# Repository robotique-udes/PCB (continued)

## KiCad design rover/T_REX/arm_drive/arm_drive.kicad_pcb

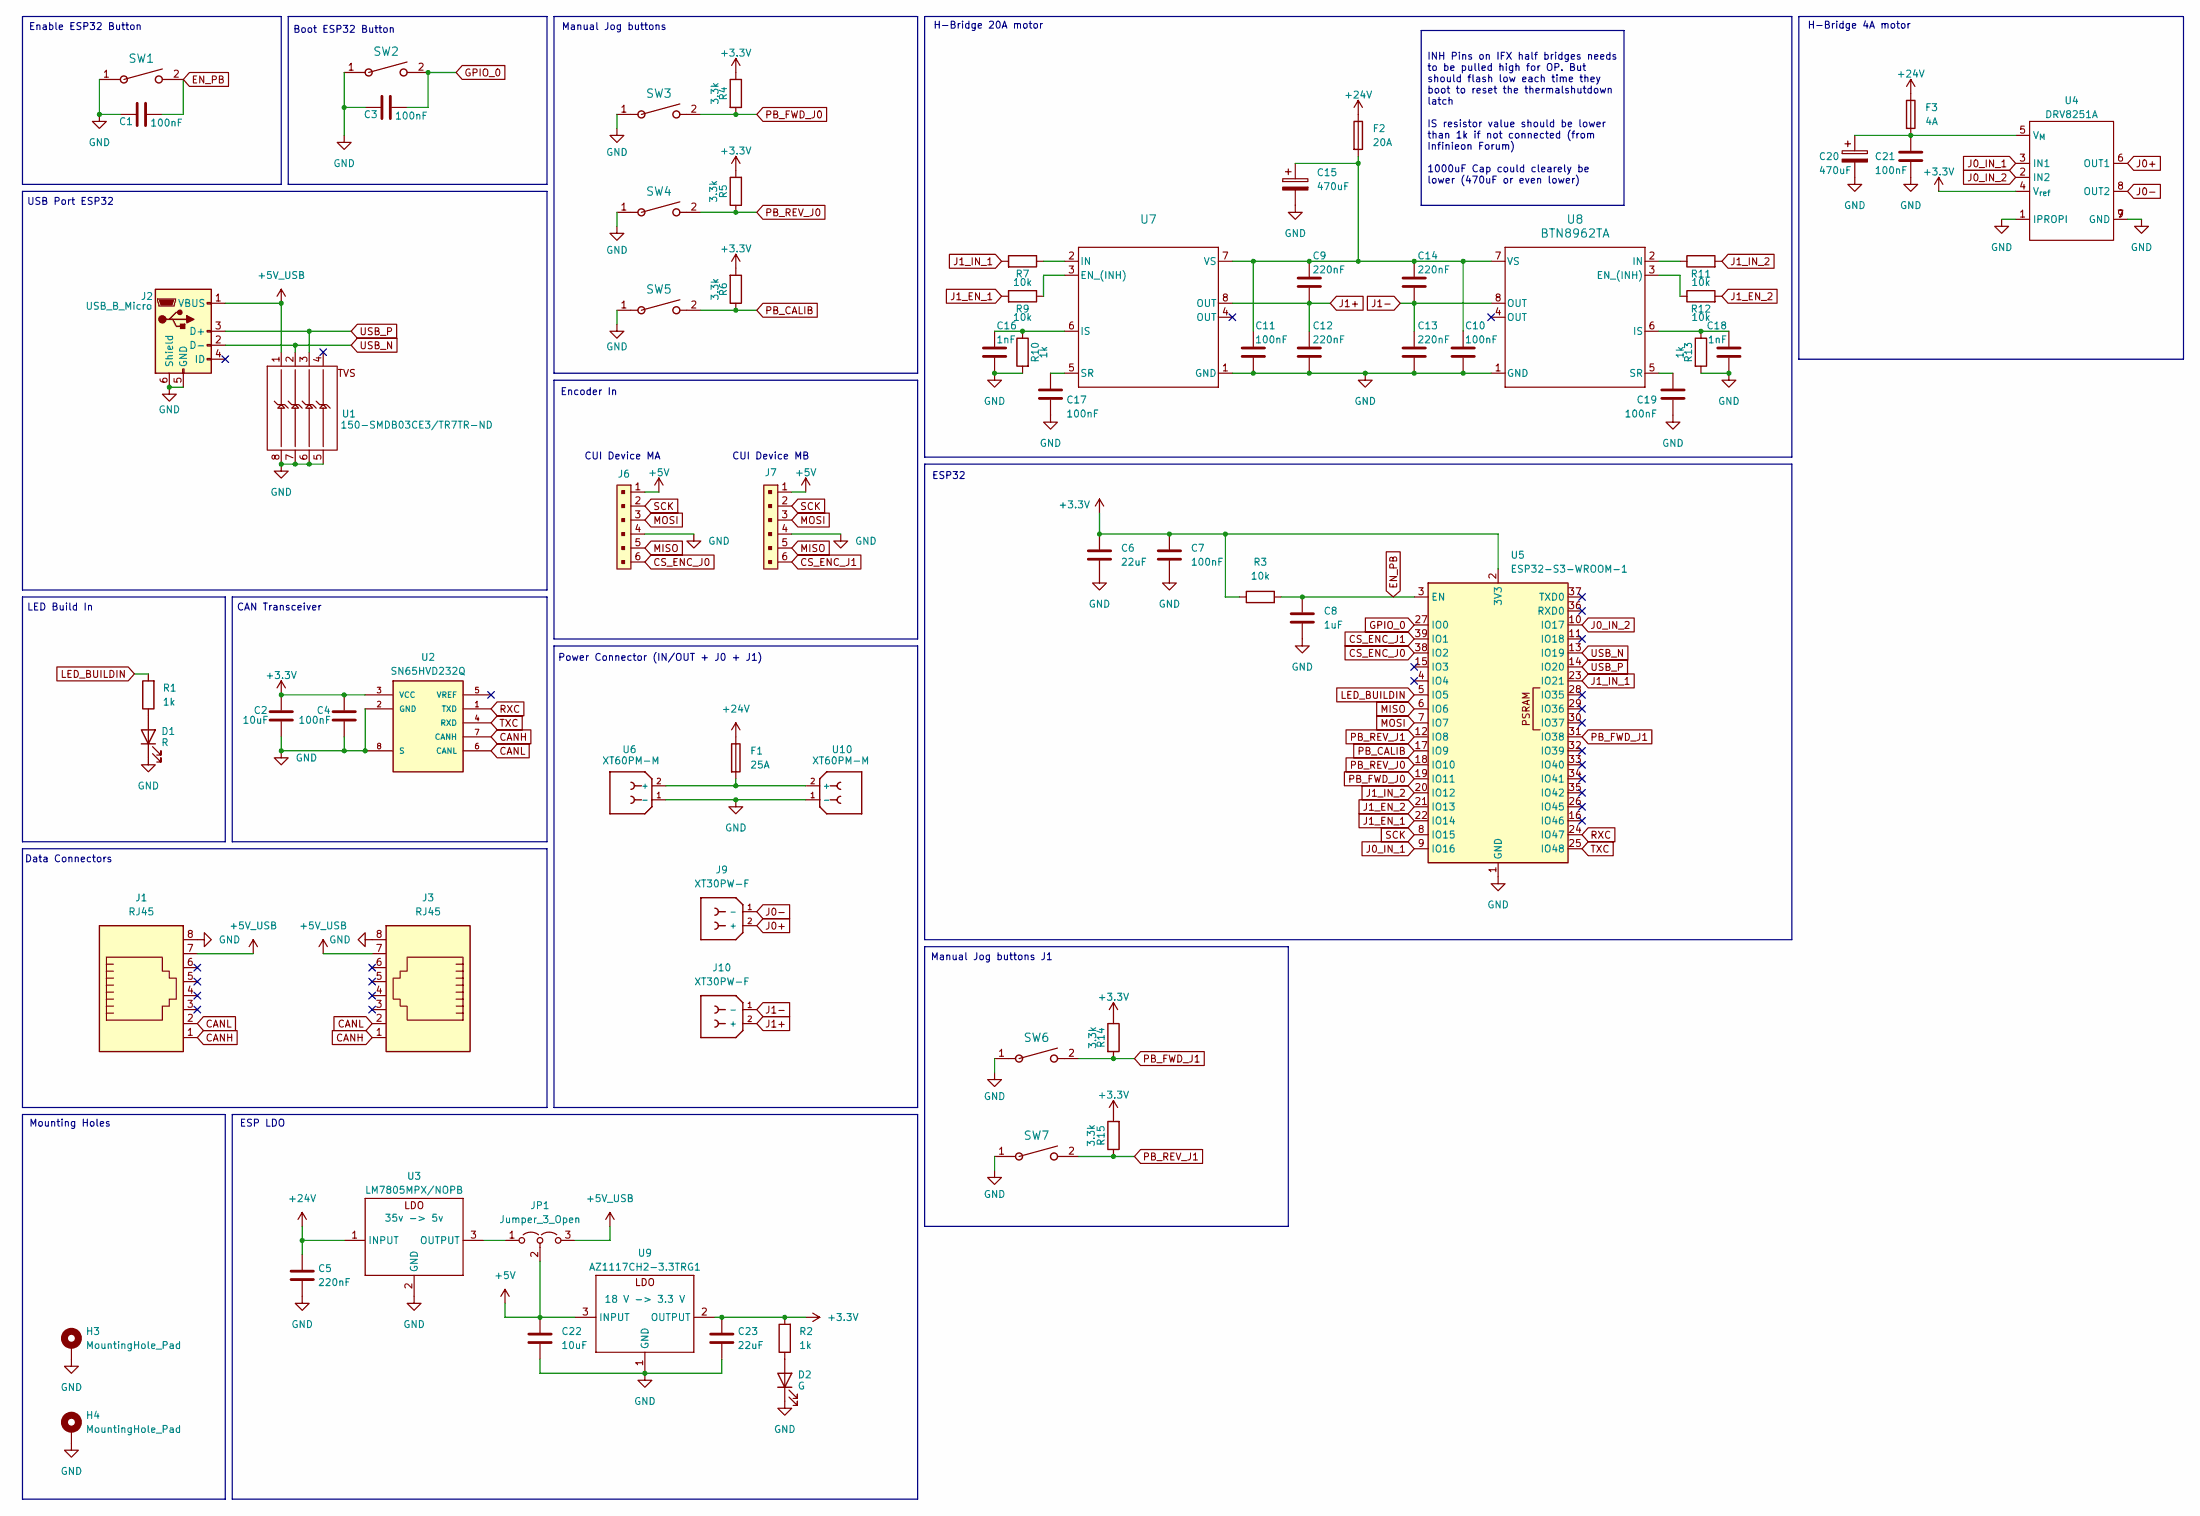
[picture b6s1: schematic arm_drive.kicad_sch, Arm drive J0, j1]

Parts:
C1, C3, C4, C7, C10, C11, C17, C19, C21: 100nF; C_0805_2012Metric_Pad1.18x1.45mm_HandSolder
C2, C22: 10uF; C_0805_2012Metric_Pad1.18x1.45mm_HandSolder
C5, C9, C12, C13, C14: 220nF; C_0805_2012Metric_Pad1.18x1.45mm_HandSolder
C6, C23: 22uF; C_0805_2012Metric_Pad1.18x1.45mm_HandSolder
C8: 1uF; C_0805_2012Metric_Pad1.18x1.45mm_HandSolder
C15, C20: 470uF; CP_Radial_D8.0mm_P3.50mm
C16, C18: 1nF; C_0805_2012Metric_Pad1.18x1.45mm_HandSolder
D1: R; LED_0805_2012Metric_Pad1.15x1.40mm_HandSolder
D2: G; LED_0805_2012Metric_Pad1.15x1.40mm_HandSolder
F1: 25A; FUSE_3568-20
F2: 20A; FUSE_3568-20
F3: 4A; FUSE_3568-20
H3, H4: MountingHole_Pad; MountingHole_3.2mm_M3_DIN965_Pad_TopBottom
J1: RJ45; ASSMANN_A-2014-2-4-N-T-R
J2: USB_B_Micro; USB_Micro-B_Amphenol_10118193-0001LF_Horizontal
J3: RJ45; AMPHENOL_54601-908WPLF
J6, J7: JST_XH_B6B-XH-AM_1x06_P2.50mm_Vertical
J9, J10: XT30PW-F; AMASS_XT30PW-F_1x02_P2.50mm_Horizontal; PARTREV 1.2
JP1: Jumper_3_Open; PinHeader_1x03_P2.54mm_Vertical
R1, R2, R10, R13: 1k; R_0805_2012Metric_Pad1.20x1.40mm_HandSolder
R3, R7, R9, R11, R12: 10k; R_0805_2012Metric_Pad1.20x1.40mm_HandSolder
R4, R5, R6, R14, R15: 3.3k; R_0805_2012Metric_Pad1.20x1.40mm_HandSolder
SW1, SW2, SW3, SW4, SW5, SW6, SW7: TS09-63-25-WT-160-SMT-TR; SW_TS09-63-25_CUD
U1: 150-SMDB03CE3/TR7TR-ND; SOIC-8-1EP_3.9x4.9mm_P1.27mm_EP2.29x3mm
U2: SN65HVD232Q; SOIC127P600X175-8N; PARTREV 4
U3: LM7805MPX/NOPB; SOT-223-3_TabPin2
U4: DRV8251A; Texas_HSOP-8-1EP_3.9x4.9mm_P1.27mm_ThermalVias
U5: ESP32-S3-WROOM-1
U6, U10: XT60PM-M; AMASS_XT60-M_1x02_P7.20mm_Vertical
U7, U8: BTN8962TA; PG-TO263-7-1_INF-M
U9: AZ1117CH2-3.3TRG1; SOT-223-3_TabPin2

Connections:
+3.3V: C2.1, C4.1, C6.1, C7.1, C23.1, R2.2, R3.1, R4.1, R5.2, R6.2, R14.1, R15.2, U2.3 (VCC), U4.4 (V_{ref}), U5.2 (3V3), U9.2 (OUTPUT)
+5V: C22.1, J6.1, J7.1, JP1.2 (C), U9.3 (INPUT)
+5V_USB: J1.7, J2.1 (VBUS), J3.7, JP1.3 (B), U1.1
+24V: C5.1, F1.1, F2.1, F3.1, U3.1 (INPUT)
CANH: J1.1, J3.1, U2.7 (CANH)
CANL: J1.2, J3.2, U2.6 (CANL)
CS_ENC_J0: J6.6, U5.38 (IO2)
CS_ENC_J1: J7.6, U5.39 (IO1)
EN_PB: C1.2, C8.1, R3.2, SW1.2, U5.3 (EN)
GND: C1.1, C2.2, C3.1, C4.2, C5.2, C6.2, C7.2, C8.2, C10.2, C11.2, C12.2, C13.2, C15.2, C16.2, C17.2, C18.2, C19.2, C20.2, C21.2, C22.2, C23.2, D1.1 (K), D2.1 (K), H3.1, H4.1, J1.8, J2.5 (GND), J2.6 (Shield), J3.8, J6.4, J7.4, R10.2, R13.2, SW1.1, SW2.1, SW3.1, SW4.1, SW5.1, SW6.1, SW7.1, U1.5, U1.6, U1.7, U1.8, U2.2 (GND), U2.8 (S), U3.2 (GND), U4.1 (IPROPI), U4.7 (GND), U4.9 (GND), U5.1 (GND), U5.40 (GND), U5.41 (GND), U6.1 (-), U7.1 (GND), U8.1 (GND), U9.1 (GND), U10.1 (-)
GPIO_0: C3.2, SW2.2, U5.27 (IO0)
J0+: J9.2 (+), U4.6 (OUT1)
J0-: J9.1 (-), U4.8 (OUT2)
J0_IN_1: U4.3 (IN1), U5.9 (IO16)
J0_IN_2: U4.2 (IN2), U5.10 (IO17)
J1+: C9.2, C12.1, J10.2 (+), U7.8 (OUT)
J1-: C13.1, C14.2, J10.1 (-), U8.8 (OUT)
J1_EN_1: R9.2, U5.22 (IO14)
J1_EN_2: R12.2, U5.21 (IO13)
J1_IN_1: R7.2, U5.23 (IO21)
J1_IN_2: R11.2, U5.20 (IO12)
LED_BUILDIN: R1.2, U5.5 (IO5)
MISO: J6.5, J7.5, U5.6 (IO6)
MOSI: J6.3, J7.3, U5.7 (IO7)
unnamed: D1.2 (A), R1.1
unnamed: D2.2 (A), R2.1
unnamed: JP1.1 (A), U3.3 (OUTPUT)
unnamed: C20.1, C21.1, F3.2, U4.5 (V_{M})
unnamed: R9.1, U7.3 (EN_(INH))
unnamed: R7.1, U7.2 (IN)
unnamed: C16.1, R10.1, U7.6 (IS)
unnamed: C17.1, U7.5 (SR)
unnamed: C9.1, C10.1, C11.1, C14.1, C15.1, F2.2, U7.7 (VS), U8.7 (VS)
unnamed: R12.1, U8.3 (EN_(INH))
unnamed: R11.1, U8.2 (IN)
unnamed: C18.1, R13.1, U8.6 (IS)
unnamed: C19.1, U8.5 (SR)
unnamed: F1.2, U6.2 (+), U10.2 (+)
PB_CALIB: R6.1, SW5.2, U5.17 (IO9)
PB_FWD_J0: R4.2, SW3.2, U5.19 (IO11)
PB_FWD_J1: R14.2, SW6.2, U5.31 (IO38)
PB_REV_J0: R5.1, SW4.2, U5.18 (IO10)
PB_REV_J1: R15.1, SW7.2, U5.12 (IO8)
RXC: U2.1 (TXD), U5.24 (IO47)
SCK: J6.2, J7.2, U5.8 (IO15)
TXC: U2.4 (RXD), U5.25 (IO48)
USB_N: J2.2 (D-), U1.2, U5.13 (IO19)
USB_P: J2.3 (D+), U1.3, U5.14 (IO20)

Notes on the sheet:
INH Pins on IFX half bridges needs to be pulled high for OP. But should flash low each time they boot to reset the thermalshutdown latch IS resistor value should be lower than 1k if not connected (from Infinieon Forum) 1000uF Cap could clearely be lower (470uF or even lower)
Boot ESP32 Button
LED Build In
Enable ESP32 Button
CAN Transceiver
Encoder In
Power Connector (IN/OUT + J0 + J1)
ESP LDO
CUI Device MB
Manual Jog buttons
Data Connectors
H-Bridge 20A motor
Mounting Holes
USB Port ESP32
CUI Device MA
Manual Jog buttons J1
H-Bridge 4A motor
ESP32

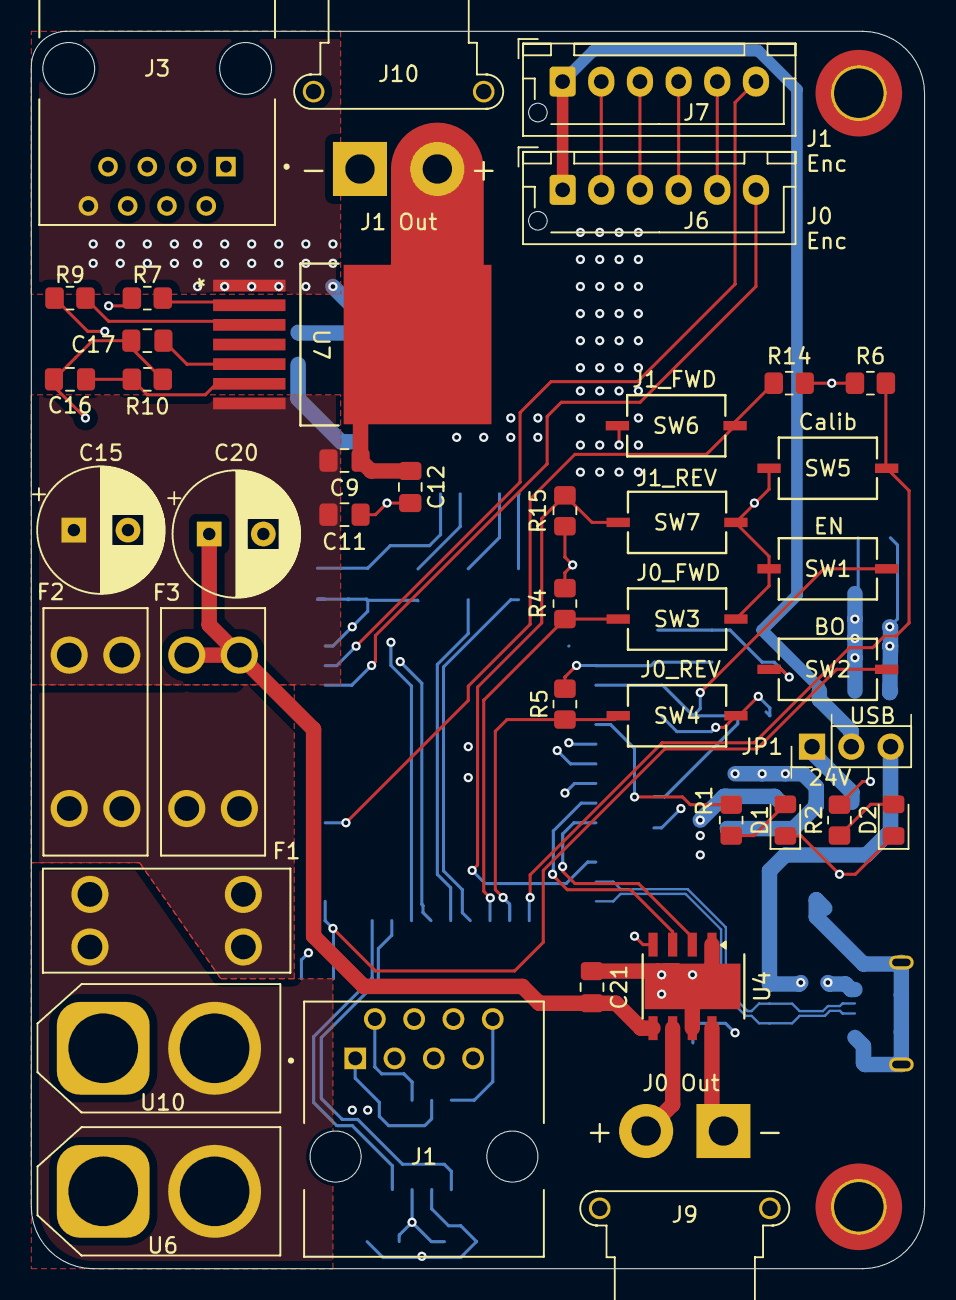
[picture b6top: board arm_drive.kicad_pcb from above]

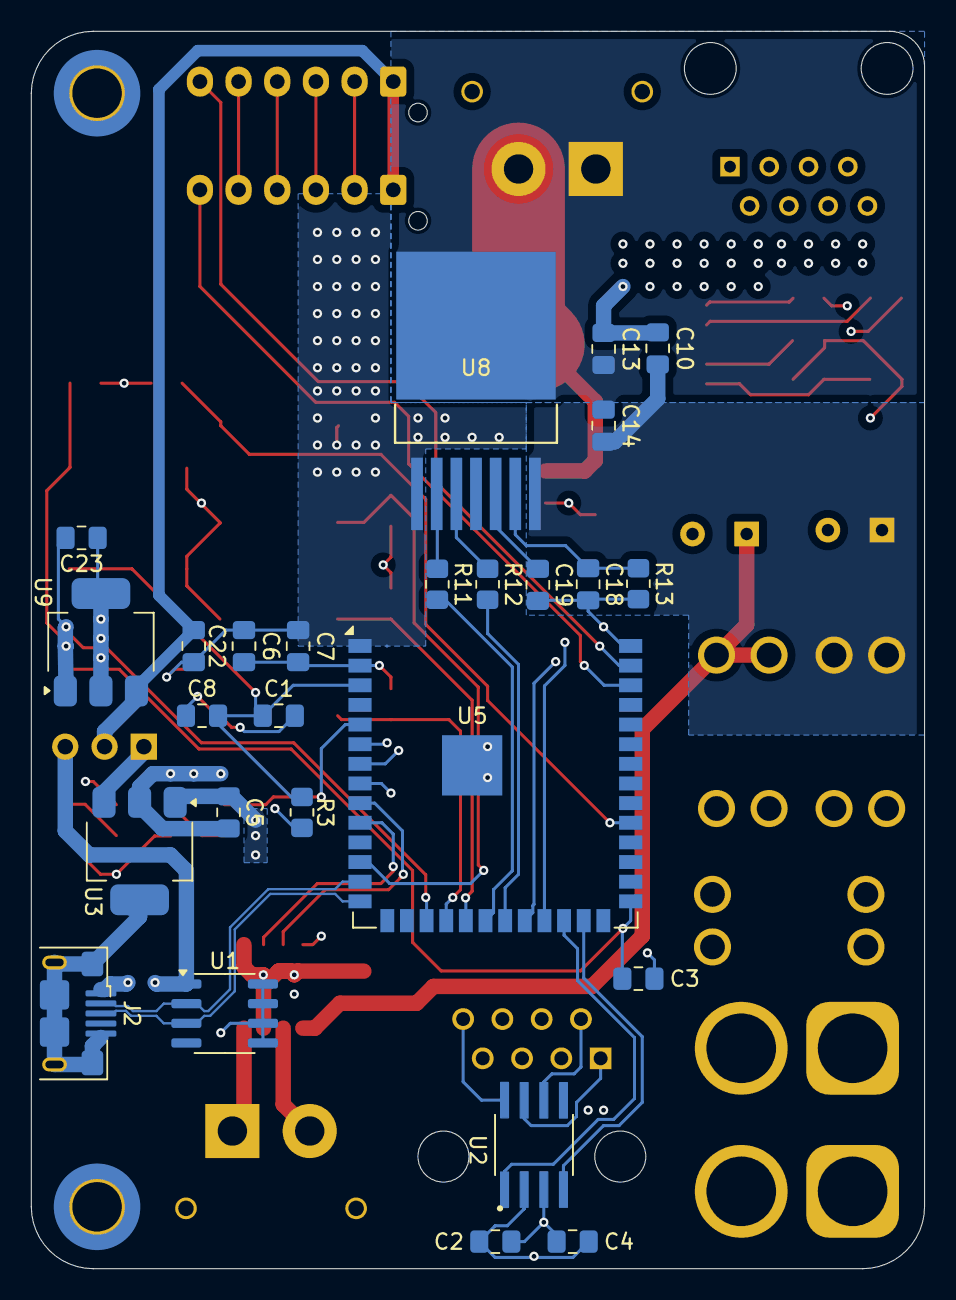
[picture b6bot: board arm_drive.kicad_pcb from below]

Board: 4 copper layers, 57.8 x 80.0 mm, 69 parts (26 on the bottom side), 48 nets.

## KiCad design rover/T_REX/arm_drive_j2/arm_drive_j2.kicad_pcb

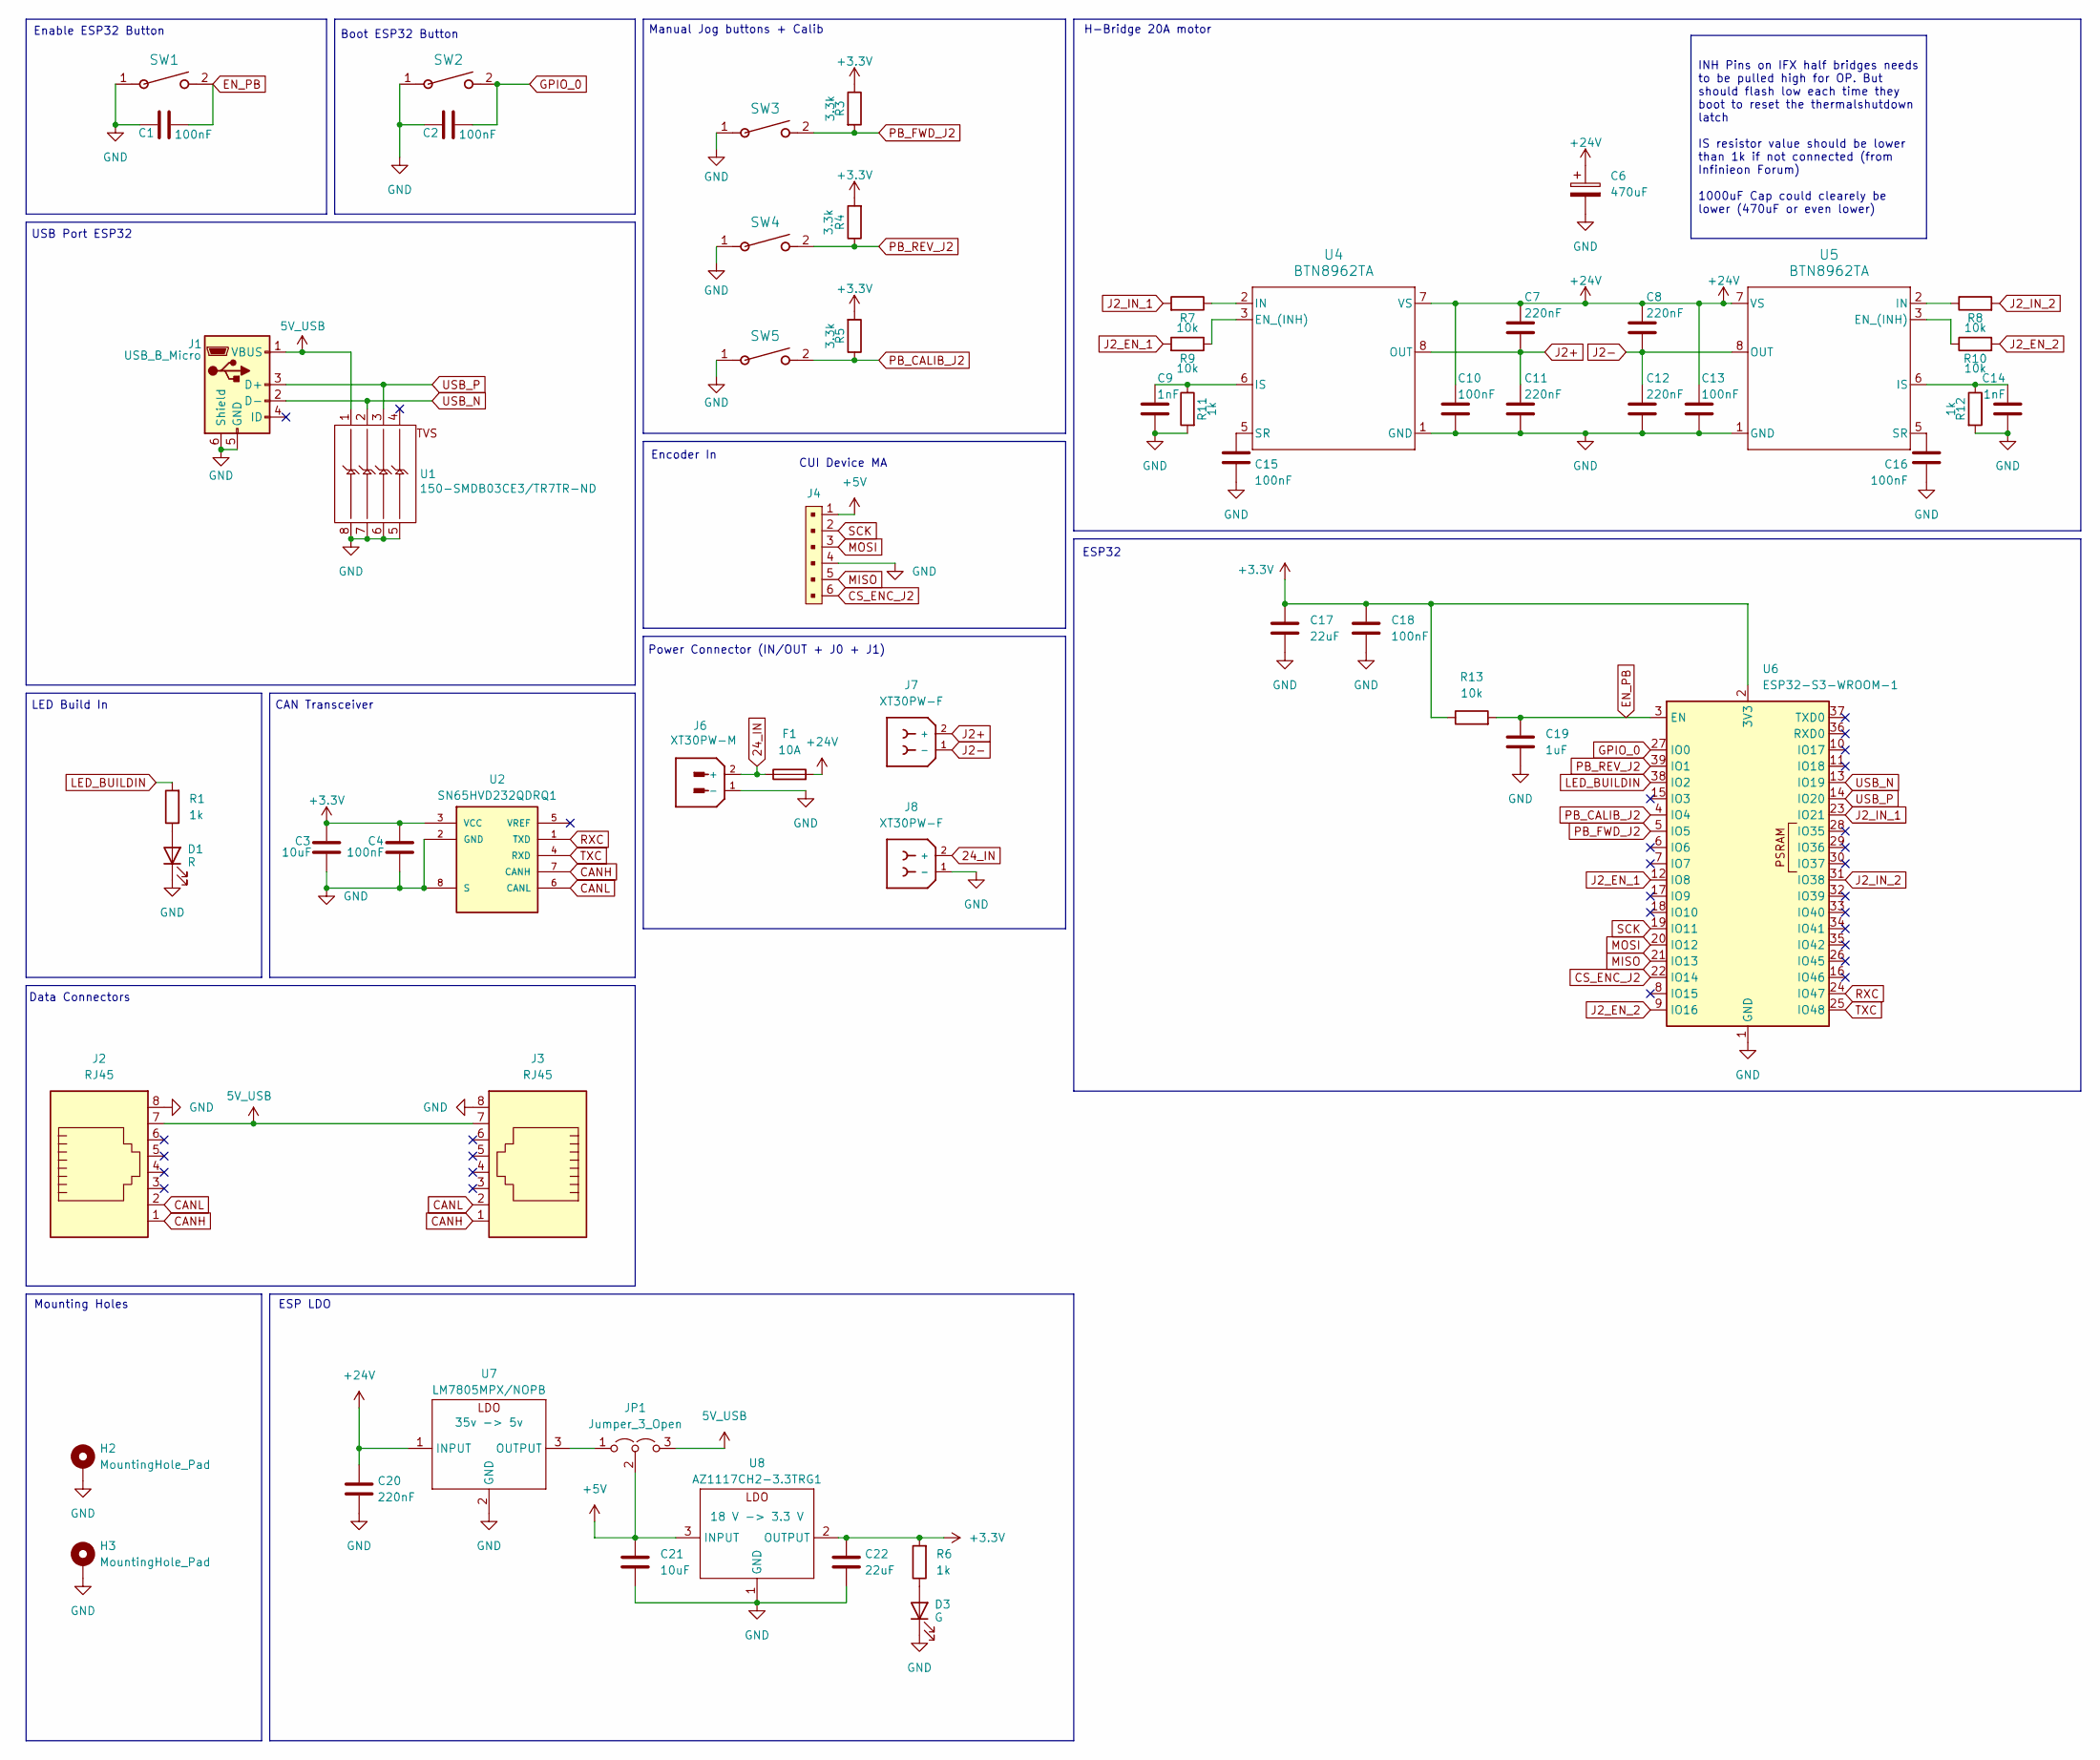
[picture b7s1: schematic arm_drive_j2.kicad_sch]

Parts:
C1, C2, C4, C10, C13, C15, C16, C18: 100nF; C_0805_2012Metric_Pad1.18x1.45mm_HandSolder
C3, C21: 10uF; C_0805_2012Metric_Pad1.18x1.45mm_HandSolder
C6: 470uF; CP_Radial_D12.5mm_P5.00mm
C7, C8, C11, C12, C20: 220nF; C_0805_2012Metric_Pad1.18x1.45mm_HandSolder
C9, C14: 1nF; C_0805_2012Metric_Pad1.18x1.45mm_HandSolder
C17, C22: 22uF; C_0805_2012Metric_Pad1.18x1.45mm_HandSolder
C19: 1uF; C_0805_2012Metric_Pad1.18x1.45mm_HandSolder
D1: R; LED_0805_2012Metric_Pad1.15x1.40mm_HandSolder
D3: G; LED_0805_2012Metric_Pad1.15x1.40mm_HandSolder
F1: 10A; FUSE_3568-20
H2, H3: MountingHole_Pad; MountingHole_2.2mm_M2_DIN965_Pad_TopBottom
J1: USB_B_Micro; USB_Micro-B_Amphenol_10118193-0001LF_Horizontal
J2, J3: RJ45; AMPHENOL_54601-908WPLF
J4: CONN_S6B-XH-SM4-TB_JST
J6: XT30PW-M; AMASS_XT30PW-M_1x02_P2.50mm_Horizontal; PARTREV 1.2
J7, J8: XT30PW-F; AMASS_XT30PW-F_1x02_P2.50mm_Horizontal; PARTREV 1.2
JP1: Jumper_3_Open; PinHeader_1x03_P2.54mm_Vertical
R1, R6, R11, R12: 1k; R_0805_2012Metric_Pad1.20x1.40mm_HandSolder
R3, R4, R5: 3.3k; R_0805_2012Metric_Pad1.20x1.40mm_HandSolder
R7, R8, R9, R10, R13: 10k; R_0805_2012Metric_Pad1.20x1.40mm_HandSolder
SW1, SW2, SW3, SW4, SW5: TS09-63-25-WT-160-SMT-TR; SW_TS09-63-25_CUD
U1: 150-SMDB03CE3/TR7TR-ND; SOIC-8-1EP_3.9x4.9mm_P1.27mm_EP2.29x3mm
U2: SN65HVD232QDRQ1; SOIC127P600X175-8N; PARTREV 4
U4, U5: BTN8962TA; PG-TO263-7-1_INF-M
U6: ESP32-S3-WROOM-1
U7: LM7805MPX/NOPB; SOT-223-3_TabPin2
U8: AZ1117CH2-3.3TRG1; SOT-223-3_TabPin2

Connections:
5V_USB: J1.1 (VBUS), J2.7, J3.7, JP1.3 (B), U1.1
24_IN: F1.1, J6.2 (+), J8.2 (+)
+3.3V: C3.1, C4.1, C17.1, C18.1, C22.1, R3.1, R4.2, R5.2, R6.2, R13.1, U2.3 (VCC), U6.2 (3V3), U8.2 (OUTPUT)
+5V: C21.1, J4.1, JP1.2 (C), U8.3 (INPUT)
+24V: C6.1, C7.1, C8.1, C10.1, C13.1, C20.1, F1.2, U4.7 (VS), U5.7 (VS), U7.1 (INPUT)
CANH: J2.1, J3.1, U2.7 (CANH)
CANL: J2.2, J3.2, U2.6 (CANL)
CS_ENC_J2: J4.6, U6.22 (IO14)
EN_PB: C1.2, C19.1, R13.2, SW1.2, U6.3 (EN)
GND: C1.1, C2.1, C3.2, C4.2, C6.2, C9.2, C10.2, C11.2, C12.2, C13.2, C14.2, C15.2, C16.2, C17.2, C18.2, C19.2, C20.2, C21.2, C22.2, D1.1 (K), D3.1 (K), H2.1, H3.1, J1.5 (GND), J1.6 (Shield), J2.8, J3.8, J4.4, J6.1 (-), J8.1 (-), R11.2, R12.2, SW1.1, SW2.1, SW3.1, SW4.1, SW5.1, U1.5, U1.6, U1.7, U1.8, U2.2 (GND), U2.8 (S), U4.1 (GND), U5.1 (GND), U6.1 (GND), U6.40 (GND), U6.41 (GND), U7.2 (GND), U8.1 (GND)
GPIO_0: C2.2, SW2.2, U6.27 (IO0)
J2+: C7.2, C11.1, J7.2 (+), U4.8 (OUT)
J2-: C8.2, C12.1, J7.1 (-), U5.8 (OUT)
J2_EN_1: R9.2, U6.12 (IO8)
J2_EN_2: R10.2, U6.9 (IO16)
J2_IN_1: R7.2, U6.23 (IO21)
J2_IN_2: R8.2, U6.31 (IO38)
LED_BUILDIN: R1.2, U6.38 (IO2)
MISO: J4.5, U6.21 (IO13)
MOSI: J4.3, U6.20 (IO12)
unnamed: D1.2 (A), R1.1
unnamed: D3.2 (A), R6.1
unnamed: JP1.1 (A), U7.3 (OUTPUT)
unnamed: R9.1, U4.3 (EN_(INH))
unnamed: R7.1, U4.2 (IN)
unnamed: C9.1, R11.1, U4.6 (IS)
unnamed: C15.1, U4.5 (SR)
unnamed: R10.1, U5.3 (EN_(INH))
unnamed: R8.1, U5.2 (IN)
unnamed: C14.1, R12.1, U5.6 (IS)
unnamed: C16.1, U5.5 (SR)
PB_CALIB_J2: R5.1, SW5.2, U6.4 (IO4)
PB_FWD_J2: R3.2, SW3.2, U6.5 (IO5)
PB_REV_J2: R4.1, SW4.2, U6.39 (IO1)
RXC: U2.1 (TXD), U6.24 (IO47)
SCK: J4.2, U6.19 (IO11)
TXC: U2.4 (RXD), U6.25 (IO48)
USB_N: J1.2 (D-), U1.2, U6.13 (IO19)
USB_P: J1.3 (D+), U1.3, U6.14 (IO20)

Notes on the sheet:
INH Pins on IFX half bridges needs to be pulled high for OP. But should flash low each time they boot to reset the thermalshutdown latch IS resistor value should be lower than 1k if not connected (from Infinieon Forum) 1000uF Cap could clearely be lower (470uF or even lower)
Boot ESP32 Button
LED Build In
Enable ESP32 Button
CAN Transceiver
Encoder In
Power Connector (IN/OUT + J0 + J1)
ESP LDO
Manual Jog buttons + Calib
Data Connectors
H-Bridge 20A motor
Mounting Holes
USB Port ESP32
CUI Device MA
ESP32

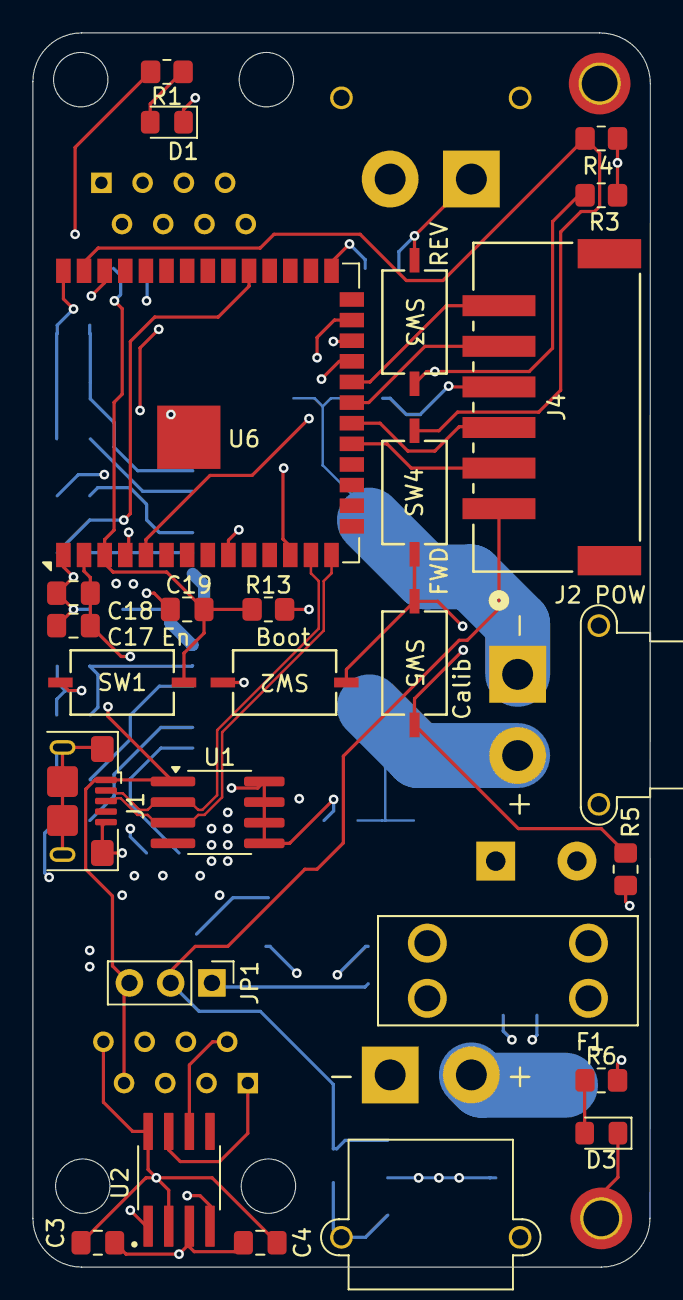
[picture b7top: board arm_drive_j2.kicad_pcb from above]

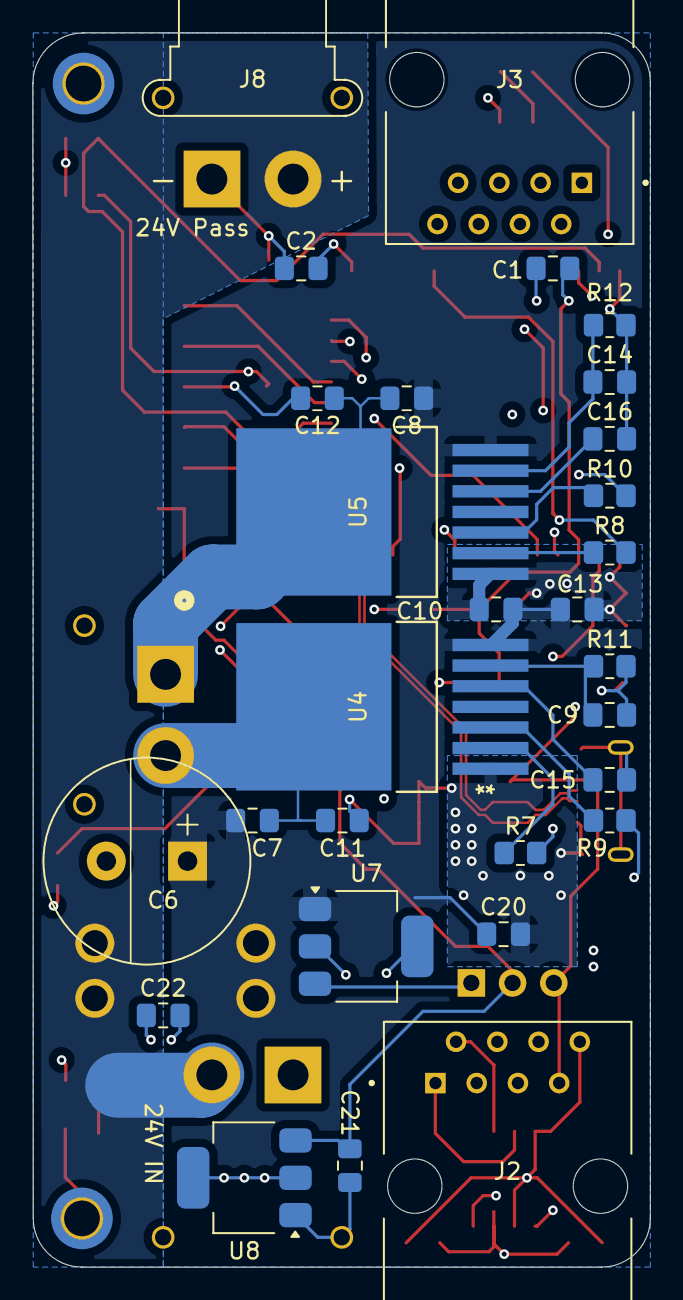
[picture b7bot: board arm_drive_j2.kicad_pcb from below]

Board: 4 copper layers, 38.0 x 76.0 mm, 58 parts (29 on the bottom side), 39 nets.

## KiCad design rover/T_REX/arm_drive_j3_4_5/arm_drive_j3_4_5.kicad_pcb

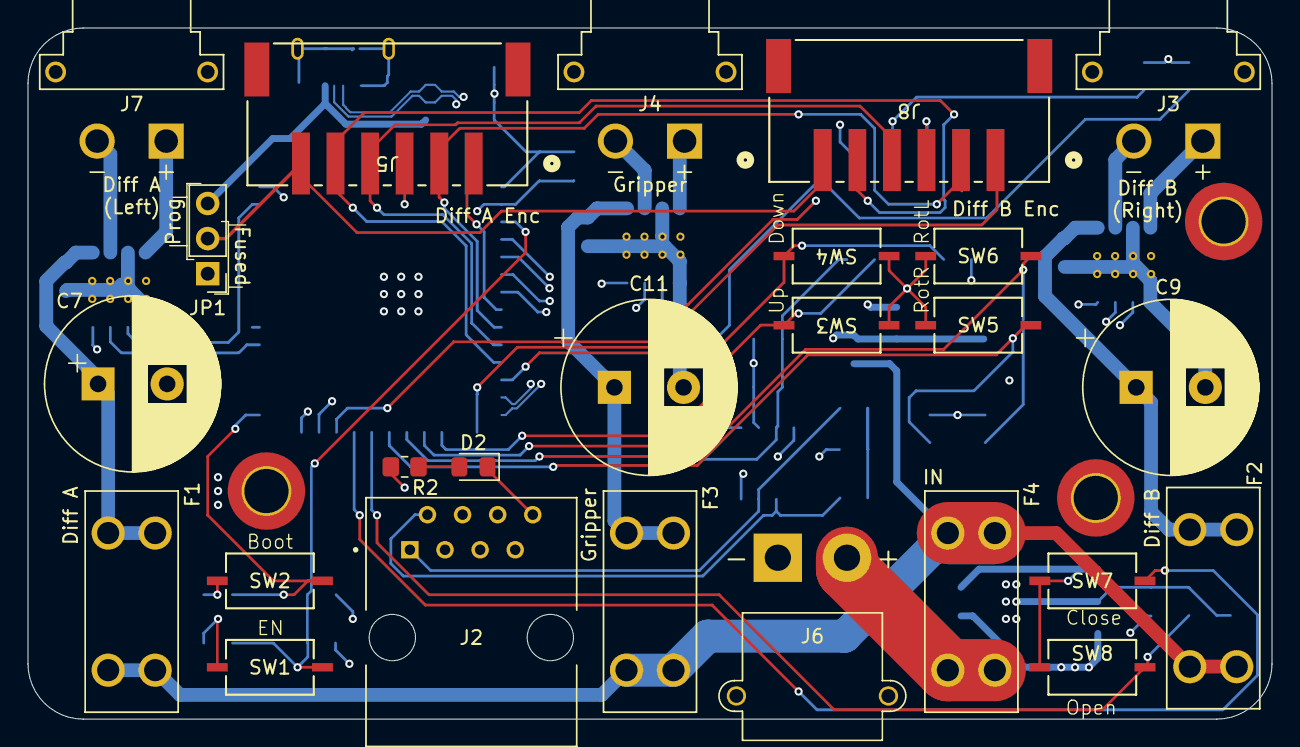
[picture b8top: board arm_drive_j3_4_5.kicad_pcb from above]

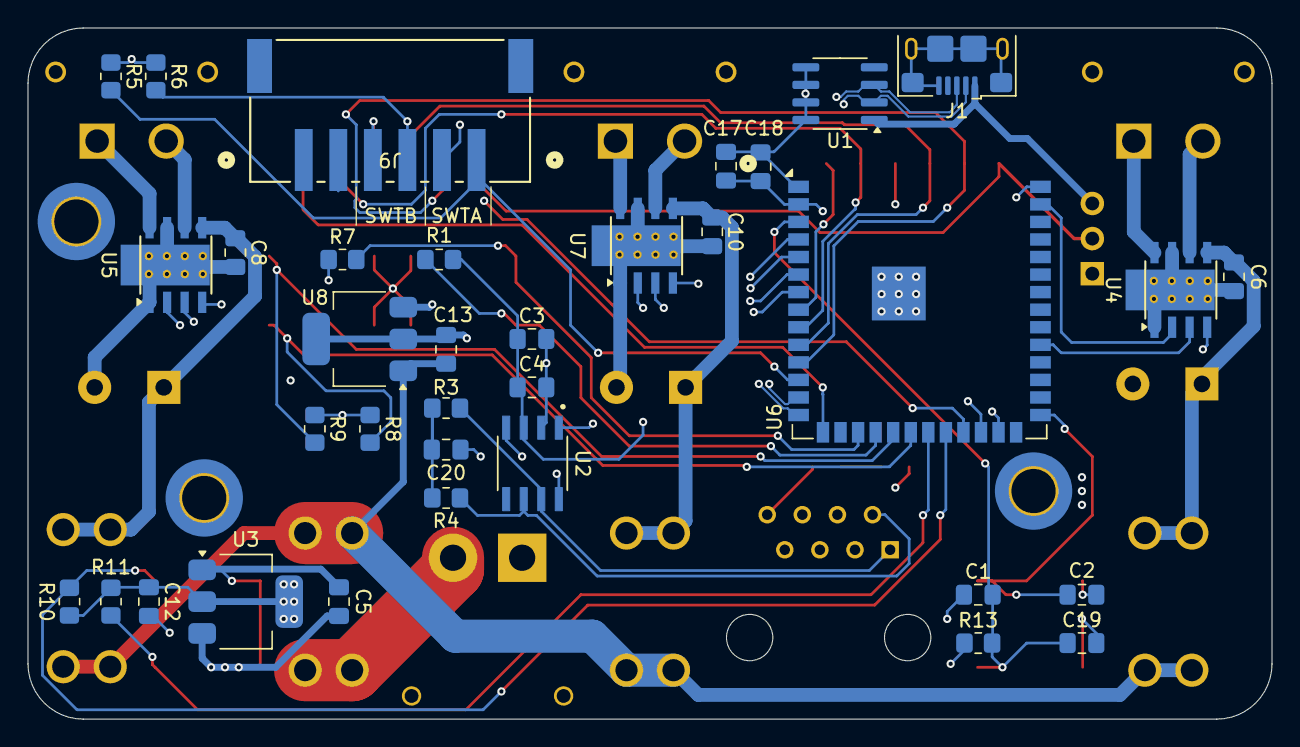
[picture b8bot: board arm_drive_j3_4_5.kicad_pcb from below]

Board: 4 copper layers, 90.0 x 50.0 mm, 63 parts (35 on the bottom side), 45 nets.

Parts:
C1, C2, C4, C6, C8, C10, C18: 100nF; C_0805_2012Metric_Pad1.18x1.45mm_HandSolder
C3, C5: 10uF; C_0805_2012Metric_Pad1.18x1.45mm_HandSolder
C7, C9, C11: 470uF; CP_Radial_D12.5mm_P5.00mm
C12, C17: 22uF; C_0805_2012Metric_Pad1.18x1.45mm_HandSolder
C13: 220nF; C_0805_2012Metric_Pad1.18x1.45mm_HandSolder
C19: 1uF; C_0805_2012Metric_Pad1.18x1.45mm_HandSolder
C20: 47nF; C_0805_2012Metric_Pad1.18x1.45mm_HandSolder
D2: G; LED_0805_2012Metric_Pad1.15x1.40mm_HandSolder
F1, F2, F3: 4A; FUSE_3568-20
F4: 9A; FUSE_3568-20
H2, H3, H4: MountingHole_Pad; MountingHole_3.2mm_M3_DIN965_Pad_TopBottom
J1: USB_B_Micro; USB_Micro-B_Amphenol_10118193-0001LF_Horizontal
J2: RJ45; AMPHENOL_54601-908WPLF
J3, J4, J7: XT30PW-F; AMASS_XT30PW-F
J5, J8, J9: CONN_S6B-XH-SM4-TB_JST
J6: XT30PW-M; AMASS_XT30PW-M_1x02_P2.50mm_Horizontal
JP1: Jumper_3_Open; PinHeader_1x03_P2.54mm_Vertical
R1, R5, R6, R7, R8, R9, R10, R11: 3.3k; R_0805_2012Metric_Pad1.20x1.40mm_HandSolder
R2: 1k; R_0805_2012Metric_Pad1.20x1.40mm_HandSolder
R3, R4: 60; R_0805_2012Metric_Pad1.20x1.40mm_HandSolder
R13: 10k; R_0805_2012Metric_Pad1.20x1.40mm_HandSolder
SW1, SW2, SW3, SW4, SW5, SW6, SW7, SW8: TS09-63-25-WT-160-SMT-TR; SW_TS09-63-25_CUD
U1: SOIC-8-1EP_3.9x4.9mm_P1.27mm_EP2.29x3mm
U2: SN65HVD232QDRQ1; SOIC127P600X175-8N
U3: AZ1117CH2-3.3TRG1; SOT-223-3_TabPin2
U4, U5, U7: DRV8251A; Texas_HSOP-8-1EP_3.9x4.9mm_P1.27mm_ThermalVias
U6: ESP32-S3-WROOM-1
U8: LM7805MPX/NOPB; SOT-223-3_TabPin2

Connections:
+3.3V: C3.1, C4.1, C12.1, C17.1, C18.1, R1.1, R2.2, R5.1, R6.1, R7.1, R8.1, R9.1, R10.1, R11.1, R13.1, U2.3 (VCC), U3.2 (OUTPUT), U4.4 (V_{ref}), U5.4 (V_{ref}), U6.2 (3V3), U7.4 (V_{ref})
+5V: C5.1, J5.6, J8.6, JP1.2 (C), U3.3 (INPUT)
+5V_USB: J1.1 (VBUS), J2.7, JP1.3 (B), U1.1
+24V: C13.1, F1.2, F2.2, F3.2, F4.1, U8.1 (INPUT)
CANH: J2.1, R3.2, U2.7 (CANH)
CANL: J2.2, R4.1, U2.6 (CANL)
CS_ENC_DIFF_A: J5.1, U6.8 (IO15)
CS_ENC_DIFF_B: J8.1, U6.15 (IO3)
CS_SWT_A_GRIP: J9.3, R6.2, U6.23 (IO21)
CS_SWT_B_GRIP: J9.1, R5.2, U6.12 (IO8)
Diff_A+: J7.2 (-), U4.6 (OUT1)
Diff_A-: J7.1 (+), U4.8 (OUT2)
Diff_A_IN_1: U4.3 (IN1), U6.31 (IO38)
Diff_A_IN_2: U4.2 (IN2), U6.39 (IO1)
Diff_B+: J3.2 (-), U5.6 (OUT1)
Diff_B-: J3.1 (+), U5.8 (OUT2)
Diff_B_IN_1: U5.3 (IN1), U6.6 (IO6)
Diff_B_IN_2: U5.2 (IN2), U6.7 (IO7)
EN_PB: C1.2, C19.1, R13.2, SW1.2, U6.3 (EN)
GND: C1.1, C2.1, C3.2, C4.2, C5.2, C6.2, C7.2, C8.2, C9.2, C10.2, C11.2, C12.2, C13.2, C17.2, C18.2, C19.2, C20.1, D2.1 (K), H2.1, H3.1, H4.1, J1.5 (GND), J1.6 (Shield), J2.8, J5.3, J6.1 (-), J8.3, J9.2, J9.4, SW1.1, SW2.1, SW3.1, SW4.1, SW5.1, SW6.1, SW7.1, SW8.1, U1.5, U1.6, U1.7, U1.8, U2.2 (GND), U2.8 (S), U3.1 (GND), U4.1 (IPROPI), U4.7 (GND), U4.9 (GND), U5.1 (IPROPI), U5.7 (GND), U5.9 (GND), U6.1 (GND), U6.40 (GND), U6.41 (GND), U7.1 (IPROPI), U7.7 (GND), U7.9 (GND), U8.2 (GND)
GPIO_0: C2.2, SW2.2, U6.27 (IO0)
Grip+: J4.2 (-), U7.6 (OUT1)
Grip-: J4.1 (+), U7.8 (OUT2)
Grip_IN_1: U6.4 (IO4), U7.3 (IN1)
Grip_IN_2: U6.5 (IO5), U7.2 (IN2)
MISO: J5.2, J8.2, U6.9 (IO16)
MOSI: J5.4, J8.4, U6.10 (IO17)
unnamed: C20.2, R3.1, R4.2
unnamed: D2.2 (A), R2.1
unnamed: F4.2, J6.2 (+)
unnamed: JP1.1 (A), U8.3 (OUTPUT)
unnamed: C6.1, C7.1, F1.1, U4.5 (V_{M})
unnamed: C8.1, C9.1, F2.1, U5.5 (V_{M})
unnamed: C10.1, C11.1, F3.1, U7.5 (V_{M})
PB_Diff_Down: R7.2, SW4.2, U6.17 (IO9)
PB_Diff_Left: R9.2, SW6.2, U6.19 (IO11)
PB_Diff_Right: R8.2, SW5.2, U6.20 (IO12)
PB_Diff_Up: R1.2, SW3.2, U6.18 (IO10)
PB_Grip_FWD: R10.2, SW7.2, U6.22 (IO14)
PB_Grip_REV: R11.2, SW8.2, U6.21 (IO13)
RXC: U2.1 (TXD), U6.24 (IO47)
SCK: J5.5, J8.5, U6.11 (IO18)
TXC: U2.4 (RXD), U6.25 (IO48)
USB_N: J1.2 (D-), U1.2, U6.13 (IO19)
USB_P: J1.3 (D+), U1.3, U6.14 (IO20)
